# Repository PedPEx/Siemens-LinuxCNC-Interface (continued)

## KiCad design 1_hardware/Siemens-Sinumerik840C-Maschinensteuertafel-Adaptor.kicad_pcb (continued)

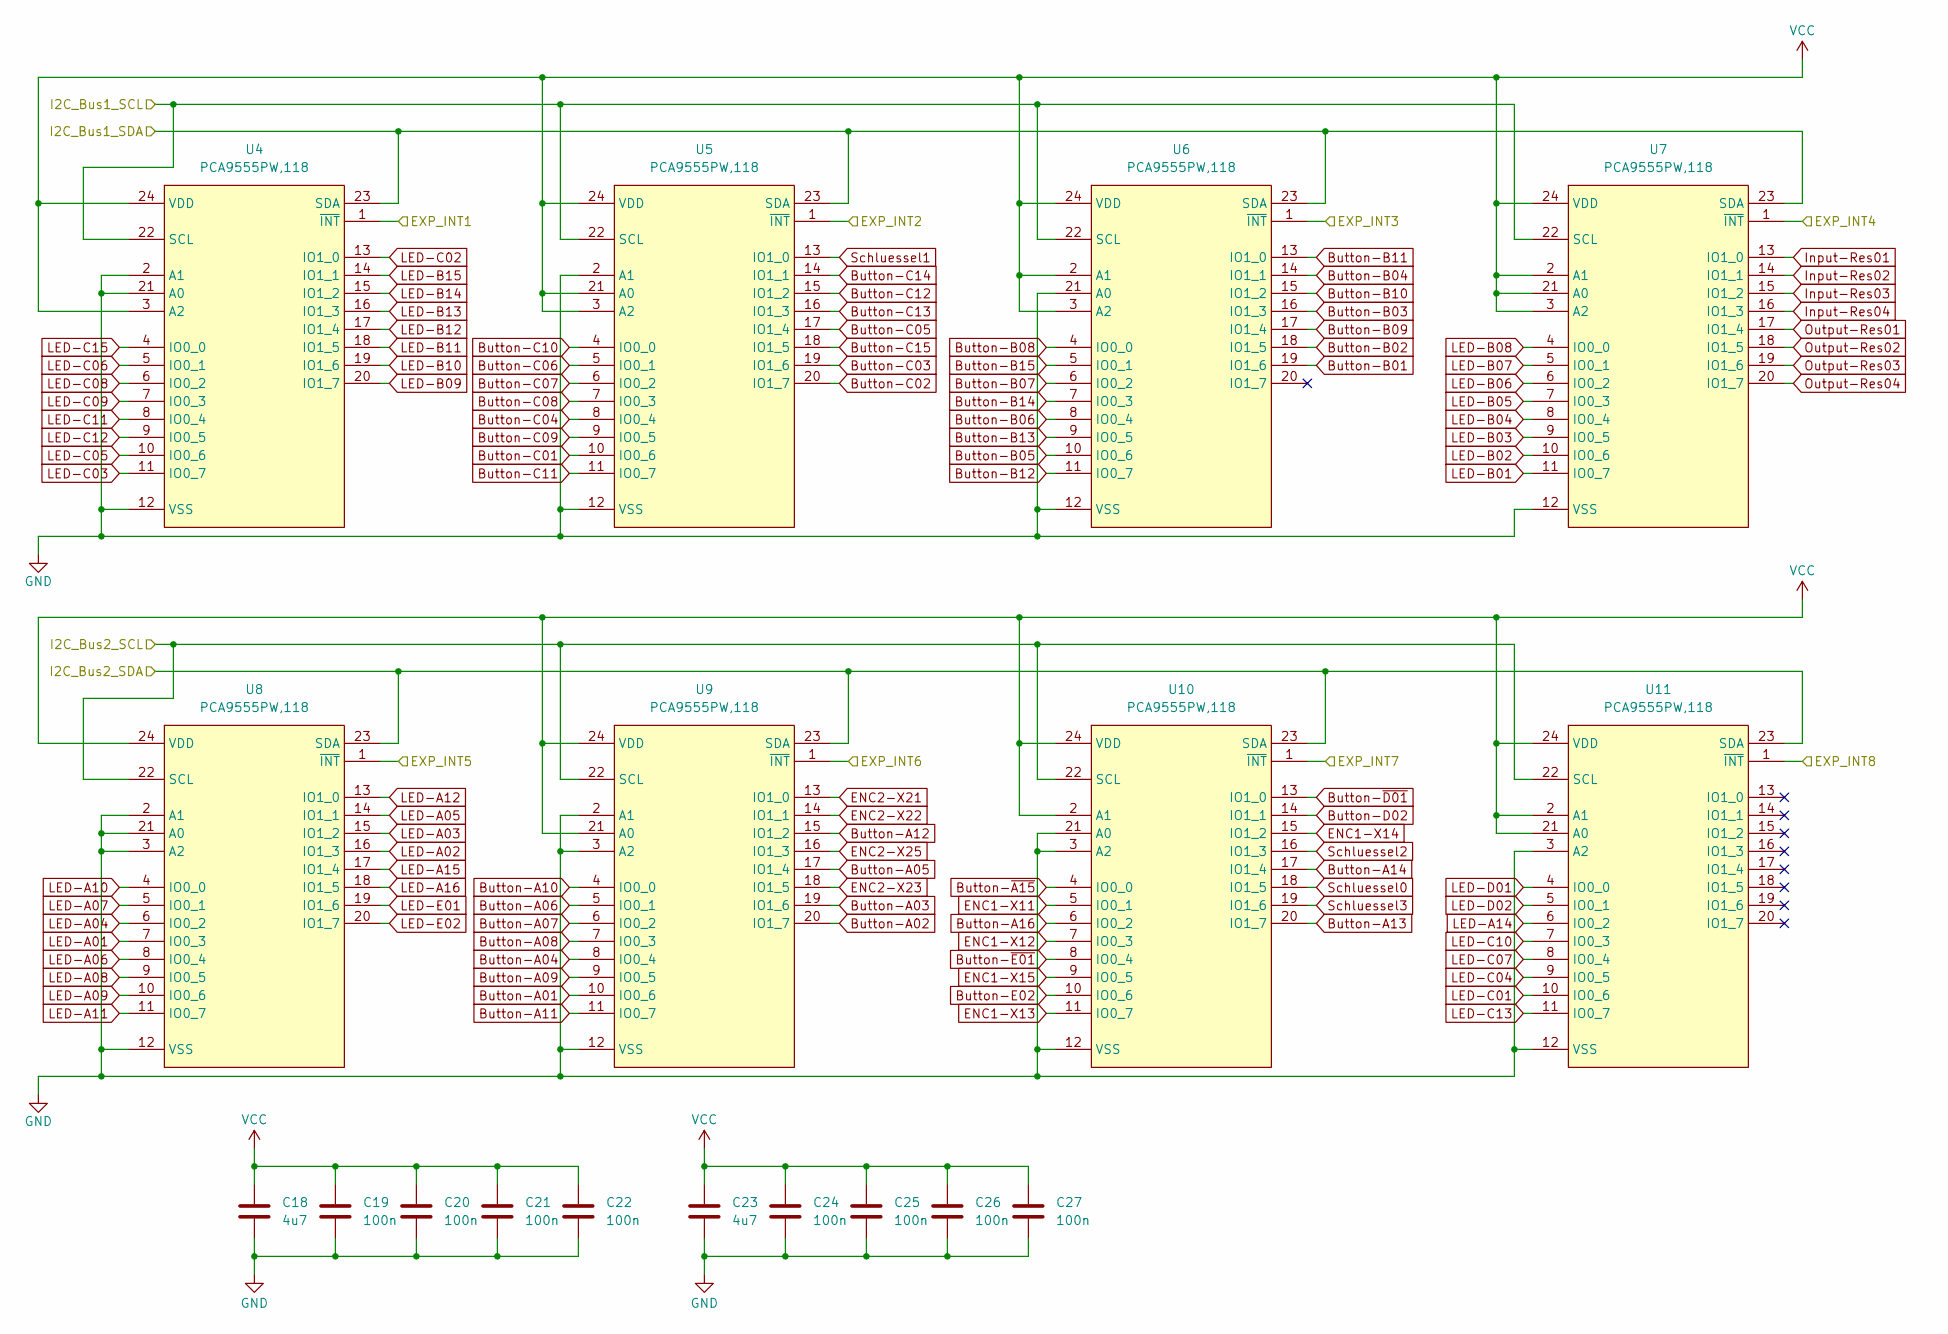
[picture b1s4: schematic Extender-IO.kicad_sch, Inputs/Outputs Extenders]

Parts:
C18, C23: 4u7; C_0603_1608Metric
C19, C20, C21, C22, C24, C25, C26, C27: 100n; C_0603_1608Metric
U4, U5, U6, U7, U8, U9, U10, U11: PCA9555PW,118; TSSOP-24_L7.8-W4.4-P0.65-LS6.4-BL; LCSC Part C128392

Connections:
Button-A01: U9.10 (IO0_6); also elsewhere on the board
Button-A02: U9.20 (IO1_7); also elsewhere on the board
Button-A03: U9.19 (IO1_6); also elsewhere on the board
Button-A04: U9.8 (IO0_4); also elsewhere on the board
Button-A05: U9.17 (IO1_4); also elsewhere on the board
Button-A06: U9.5 (IO0_1); also elsewhere on the board
Button-A07: U9.6 (IO0_2); also elsewhere on the board
Button-A08: U9.7 (IO0_3); also elsewhere on the board
Button-A09: U9.9 (IO0_5); also elsewhere on the board
Button-A10: U9.4 (IO0_0); also elsewhere on the board
Button-A11: U9.11 (IO0_7); also elsewhere on the board
Button-A12: U9.15 (IO1_2); also elsewhere on the board
Button-A13: U10.20 (IO1_7); also elsewhere on the board
Button-A14: U10.17 (IO1_4); also elsewhere on the board
Button-A16: U10.6 (IO0_2); also elsewhere on the board
Button-B01: U6.19 (IO1_6); also elsewhere on the board
Button-B02: U6.18 (IO1_5); also elsewhere on the board
Button-B03: U6.16 (IO1_3); also elsewhere on the board
Button-B04: U6.14 (IO1_1); also elsewhere on the board
Button-B05: U6.10 (IO0_6); also elsewhere on the board
Button-B06: U6.8 (IO0_4); also elsewhere on the board
Button-B07: U6.6 (IO0_2); also elsewhere on the board
Button-B08: U6.4 (IO0_0); also elsewhere on the board
Button-B09: U6.17 (IO1_4); also elsewhere on the board
Button-B10: U6.15 (IO1_2); also elsewhere on the board
Button-B11: U6.13 (IO1_0); also elsewhere on the board
Button-B12: U6.11 (IO0_7); also elsewhere on the board
Button-B13: U6.9 (IO0_5); also elsewhere on the board
Button-B14: U6.7 (IO0_3); also elsewhere on the board
Button-B15: U6.5 (IO0_1); also elsewhere on the board
Button-C01: U5.10 (IO0_6); also elsewhere on the board
Button-C02: U5.20 (IO1_7); also elsewhere on the board
Button-C03: U5.19 (IO1_6); also elsewhere on the board
Button-C04: U5.8 (IO0_4); also elsewhere on the board
Button-C05: U5.17 (IO1_4); also elsewhere on the board
Button-C06: U5.5 (IO0_1); also elsewhere on the board
Button-C07: U5.6 (IO0_2); also elsewhere on the board
Button-C08: U5.7 (IO0_3); also elsewhere on the board
Button-C09: U5.9 (IO0_5); also elsewhere on the board
Button-C10: U5.4 (IO0_0); also elsewhere on the board
Button-C11: U5.11 (IO0_7); also elsewhere on the board
Button-C12: U5.15 (IO1_2); also elsewhere on the board
Button-C13: U5.16 (IO1_3); also elsewhere on the board
Button-C14: U5.14 (IO1_1); also elsewhere on the board
Button-C15: U5.18 (IO1_5); also elsewhere on the board
Button-D02: U10.14 (IO1_1); also elsewhere on the board
Button-E02: U10.10 (IO0_6); also elsewhere on the board
Button-~A15: U10.4 (IO0_0); also elsewhere on the board
Button-~D01: U10.13 (IO1_0); also elsewhere on the board
Button-~E01: U10.8 (IO0_4); also elsewhere on the board
ENC1-X11: U10.5 (IO0_1); also elsewhere on the board
ENC1-X12: U10.7 (IO0_3); also elsewhere on the board
ENC1-X13: U10.11 (IO0_7); also elsewhere on the board
ENC1-X14: U10.15 (IO1_2); also elsewhere on the board
ENC1-X15: U10.9 (IO0_5); also elsewhere on the board
ENC2-X21: U9.13 (IO1_0); also elsewhere on the board
ENC2-X22: U9.14 (IO1_1); also elsewhere on the board
ENC2-X23: U9.18 (IO1_5); also elsewhere on the board
ENC2-X25: U9.16 (IO1_3); also elsewhere on the board
EXP_INT1: U4.1 (~INT); also elsewhere on the board
EXP_INT2: U5.1 (~INT); also elsewhere on the board
EXP_INT3: U6.1 (~INT); also elsewhere on the board
EXP_INT4: U7.1 (~INT); also elsewhere on the board
EXP_INT5: U8.1 (~INT); also elsewhere on the board
EXP_INT6: U9.1 (~INT); also elsewhere on the board
EXP_INT7: U10.1 (~INT); also elsewhere on the board
EXP_INT8: U11.1 (~INT); also elsewhere on the board
GND: C18.1, C19.1, C20.1, C21.1, C22.1, C23.1, C24.1, C25.1, C26.1, C27.1, U4.2 (A1), U4.12 (VSS), U4.21 (A0), U5.2 (A1), U5.12 (VSS), U6.12 (VSS), U6.21 (A0), U7.12 (VSS), U8.2 (A1), U8.3 (A2), U8.12 (VSS), U8.21 (A0), U9.2 (A1), U9.3 (A2), U9.12 (VSS), U10.3 (A2), U10.12 (VSS), U10.21 (A0), U11.3 (A2), U11.12 (VSS); also elsewhere on the board
I2C1_SCL: U4.22 (SCL), U5.22 (SCL), U6.22 (SCL), U7.22 (SCL); also elsewhere on the board
I2C1_SDA: U4.23 (SDA), U5.23 (SDA), U6.23 (SDA), U7.23 (SDA); also elsewhere on the board
I2C2_SCL: U8.22 (SCL), U9.22 (SCL), U10.22 (SCL), U11.22 (SCL); also elsewhere on the board
I2C2_SDA: U8.23 (SDA), U9.23 (SDA), U10.23 (SDA), U11.23 (SDA); also elsewhere on the board
Input-Res01: U7.13 (IO1_0); also elsewhere on the board
Input-Res02: U7.14 (IO1_1); also elsewhere on the board
Input-Res03: U7.15 (IO1_2); also elsewhere on the board
Input-Res04: U7.16 (IO1_3); also elsewhere on the board
LED-A01: U8.7 (IO0_3); also elsewhere on the board
LED-A02: U8.16 (IO1_3); also elsewhere on the board
LED-A03: U8.15 (IO1_2); also elsewhere on the board
LED-A04: U8.6 (IO0_2); also elsewhere on the board
LED-A05: U8.14 (IO1_1); also elsewhere on the board
LED-A06: U8.8 (IO0_4); also elsewhere on the board
LED-A07: U8.5 (IO0_1); also elsewhere on the board
LED-A08: U8.9 (IO0_5); also elsewhere on the board
LED-A09: U8.10 (IO0_6); also elsewhere on the board
LED-A10: U8.4 (IO0_0); also elsewhere on the board
LED-A11: U8.11 (IO0_7); also elsewhere on the board
LED-A12: U8.13 (IO1_0); also elsewhere on the board
LED-A14: U11.6 (IO0_2); also elsewhere on the board
LED-A15: U8.17 (IO1_4); also elsewhere on the board
LED-A16: U8.18 (IO1_5); also elsewhere on the board
LED-B01: U7.11 (IO0_7); also elsewhere on the board
LED-B02: U7.10 (IO0_6); also elsewhere on the board
LED-B03: U7.9 (IO0_5); also elsewhere on the board
LED-B04: U7.8 (IO0_4); also elsewhere on the board
LED-B05: U7.7 (IO0_3); also elsewhere on the board
LED-B06: U7.6 (IO0_2); also elsewhere on the board
LED-B07: U7.5 (IO0_1); also elsewhere on the board
LED-B08: U7.4 (IO0_0); also elsewhere on the board
LED-B09: U4.20 (IO1_7); also elsewhere on the board
LED-B10: U4.19 (IO1_6); also elsewhere on the board
LED-B11: U4.18 (IO1_5); also elsewhere on the board
LED-B12: U4.17 (IO1_4); also elsewhere on the board
LED-B13: U4.16 (IO1_3); also elsewhere on the board
LED-B14: U4.15 (IO1_2); also elsewhere on the board
LED-B15: U4.14 (IO1_1); also elsewhere on the board
LED-C01: U11.10 (IO0_6); also elsewhere on the board
LED-C02: U4.13 (IO1_0); also elsewhere on the board
LED-C03: U4.11 (IO0_7); also elsewhere on the board
LED-C04: U11.9 (IO0_5); also elsewhere on the board
LED-C05: U4.10 (IO0_6); also elsewhere on the board
LED-C06: U4.5 (IO0_1); also elsewhere on the board
LED-C07: U11.8 (IO0_4); also elsewhere on the board
LED-C08: U4.6 (IO0_2); also elsewhere on the board
LED-C09: U4.7 (IO0_3); also elsewhere on the board
LED-C10: U11.7 (IO0_3); also elsewhere on the board
LED-C11: U4.8 (IO0_4); also elsewhere on the board
LED-C12: U4.9 (IO0_5); also elsewhere on the board
LED-C13: U11.11 (IO0_7); also elsewhere on the board
LED-C15: U4.4 (IO0_0); also elsewhere on the board
LED-D01: U11.4 (IO0_0); also elsewhere on the board
LED-D02: U11.5 (IO0_1); also elsewhere on the board
LED-E01: U8.19 (IO1_6); also elsewhere on the board
LED-E02: U8.20 (IO1_7); also elsewhere on the board
Output-Res01: U7.17 (IO1_4); also elsewhere on the board
Output-Res02: U7.18 (IO1_5); also elsewhere on the board
Output-Res03: U7.19 (IO1_6); also elsewhere on the board
Output-Res04: U7.20 (IO1_7); also elsewhere on the board
Schluessel0: U10.18 (IO1_5); also elsewhere on the board
Schluessel1: U5.13 (IO1_0); also elsewhere on the board
Schluessel2: U10.16 (IO1_3); also elsewhere on the board
Schluessel3: U10.19 (IO1_6); also elsewhere on the board
VCC: C18.2, C19.2, C20.2, C21.2, C22.2, C23.2, C24.2, C25.2, C26.2, C27.2, U4.3 (A2), U4.24 (VDD), U5.3 (A2), U5.21 (A0), U5.24 (VDD), U6.2 (A1), U6.3 (A2), U6.24 (VDD), U7.2 (A1), U7.3 (A2), U7.21 (A0), U7.24 (VDD), U8.24 (VDD), U9.21 (A0), U9.24 (VDD), U10.2 (A1), U10.24 (VDD), U11.2 (A1), U11.21 (A0), U11.24 (VDD); also elsewhere on the board

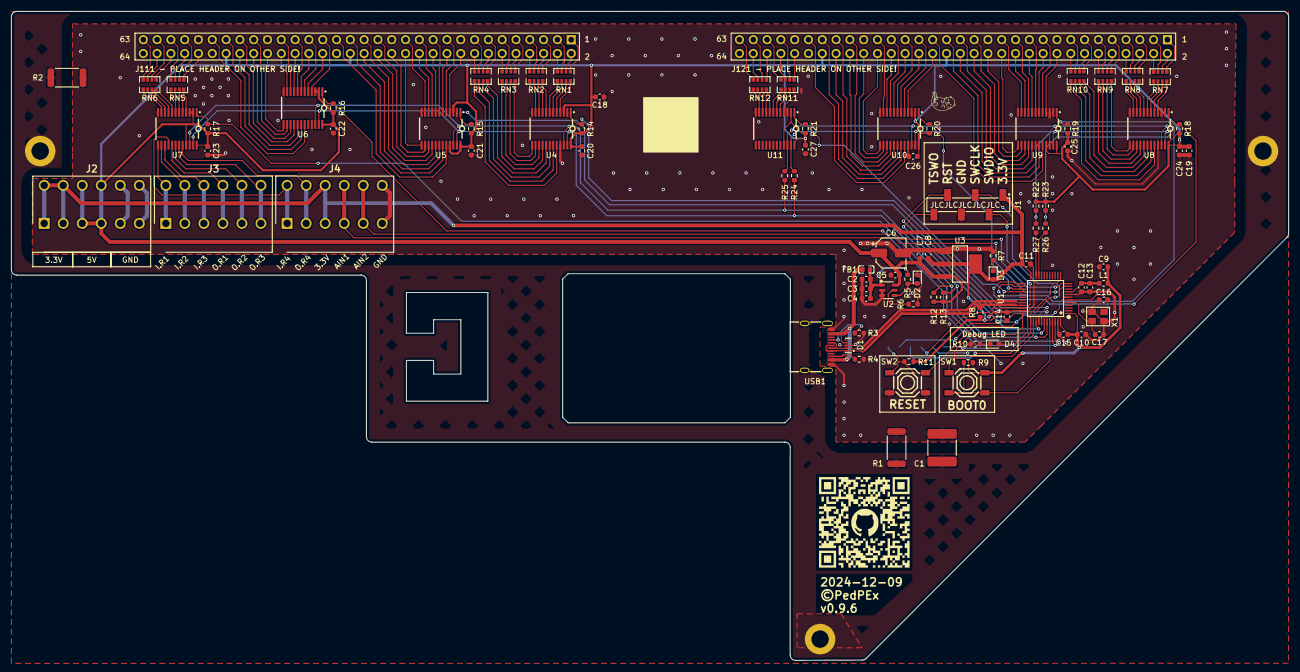
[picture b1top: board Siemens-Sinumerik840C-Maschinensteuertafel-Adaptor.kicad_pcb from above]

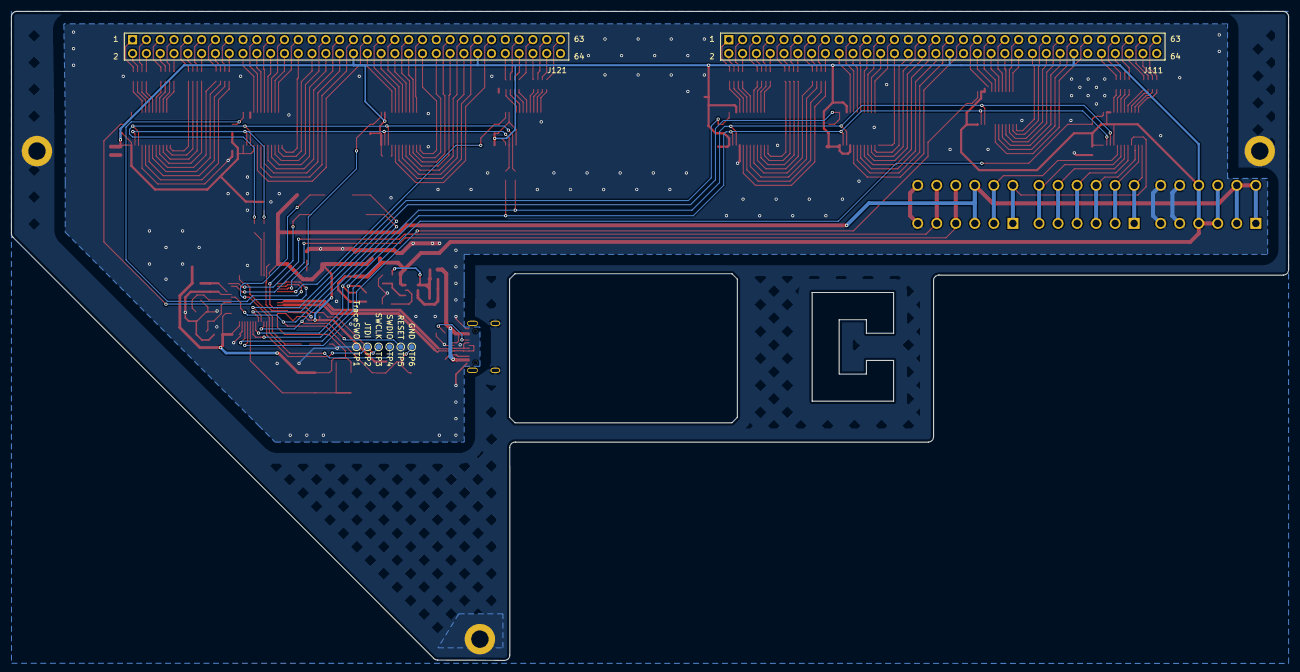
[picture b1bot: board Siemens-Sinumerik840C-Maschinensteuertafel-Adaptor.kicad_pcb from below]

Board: 2 copper layers, 235.0 x 119.4 mm, 102 parts (8 on the bottom side), 207 nets.

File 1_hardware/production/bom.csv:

Designator,Footprint,Quantity,Value,LCSC Part #
C1,2220,1,0.1u,C5290327
"C10, C11, C13, C14, C15, C19, C20, C21, C22, C24, C25, C26, C27",0603,13,100n,
"C12, C2",0603,2,1u,
"C16, C17",0603,2,8p,
"C18, C23, C9",0603,3,4u7,
"C3, C8",0603,2,10u,
"C4, C5, C7",0603,3,0.1u,
C6,CP_Elec_5x5.8,1,100u,C336771
D1,USON-10_L2.5-W1.0-P0.50-BL,1,TPD4E05U06DQAR_C138714,C138714
"D2, D3, D4",0603,3,LED,
FB1,L0603,1,100R@100MHz,C107332
J1,HDR-SMD_6P-P2.54-V-M-LS4.8_R2,1,ProgHeader,C2883763
"J111, J121",SAMTEC_SSW-132-24-L-D,2,SSW-132-24-L-D,
J2,1824460000 - LSF-SMT 3.500690 3.5SN BK TU,1,Power,
J3,1824460000 - LSF-SMT 3.500690 3.5SN BK TU,1,Buttons,
J4,1824460000 - LSF-SMT 3.500690 3.5SN BK TU,1,Reserve2,
L1,0603,1,27nH,C12100
"R1, R2",2512,2,100k, C25717
"R10, R7",0603,2,470,
"R11, R14, R15, R16, R17, R18, R19, R20, R21, R9",0603,10,10k,
"R12, R13, R22, R23, R8",0603,5,1k5,
"R24, R25, R26, R27",0603,4,0,
"R3, R4",0603,2,5k1,
R5,0603,1,680,
R6,0603,1,25k,
"RN1, RN10, RN11, RN12, RN2, RN3, RN4, RN5, RN6, RN7, RN8, RN9",RES-ARRAY-SMD_0603-8P-L3.2-W1.6-BL,12,4x680R,C12035
"SW1, SW2",SW-SMD_4P-L5.1-W5.1-P3.70-LS6.5-TL-2,2,TS-1187A-B-A-B,C318884
TP1,TestPoint_Pad_D1.0mm,1,GND,
TP2,TestPoint_Pad_D1.0mm,1,JTDI,
TP3,TestPoint_Pad_D1.0mm,1,JTMS-SWDIO,
TP4,TestPoint_Pad_D1.0mm,1,JTCK-SWCLK,
TP5,TestPoint_Pad_D1.0mm,1,JTDO-TraceSWO,
TP6,TestPoint_Pad_D1.0mm,1,RESET,
U1,LQFP-48_L7.0-W7.0-P0.50-LS9.0-BL,1,STM32L151C8T6,C9861
"U10, U11, U4, U5, U6, U7, U8, U9",TSSOP-24_L7.8-W4.4-P0.65-LS6.4-BL,8,"PCA9555PW,118",C128392
U2,SOT-23-6_L2.9-W1.6-P0.95-LS2.8-BL,1,AP22652AW6-7,C5329413
U3,SOT-223-4_L6.5-W3.5-P2.30-LS7.0-BR,1,LD1117S33CTR,C35879
USB1,USB-C-SMD_KH-TYPE-C-16P,1,KH-TYPE-C-16P,C709357
X1,CRYSTAL-SMD_4P-L3.2-W2.5-BL_SIT8008BI,1,16MHz,C498200

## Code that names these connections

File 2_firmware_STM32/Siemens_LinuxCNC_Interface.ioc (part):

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Mcu.Name=STM32L151CCTx
Mcu.Package=LQFP48
Mcu.UserName=STM32L151CCTx
PA1.Mode=IN1
PA1.Signal=ADC_IN1
PA11.Mode=Device
PA11.Signal=USB_DM
PA12.Mode=Device
PA12.Signal=USB_DP
PA13.Mode=JTAG_4_pins
PA13.Signal=SYS_JTMS-SWDIO
PA14.Mode=JTAG_4_pins
PA14.Signal=SYS_JTCK-SWCLK
PA15.Mode=JTAG_4_pins
PA15.Signal=SYS_JTDI
PA2.Mode=IN2
PA2.Signal=ADC_IN2
PA3.GPIOParameters=GPIO_Label
PA3.GPIO_Label=DebugLED
PA3.Signal=GPIO_Output
PB10.Mode=I2C
PB10.Signal=I2C2_SCL
PB11.Mode=I2C
PB11.Signal=I2C2_SDA
PB12.GPIOParameters=GPIO_Label,GPIO_ModeDefaultEXTI
PB12.GPIO_Label=Exp_Int5
PB12.GPIO_ModeDefaultEXTI=GPIO_MODE_IT_FALLING
PB12.Signal=GPXTI12
PB13.GPIOParameters=GPIO_Label,GPIO_ModeDefaultEXTI
PB13.GPIO_Label=Exp_Int6
PB13.GPIO_ModeDefaultEXTI=GPIO_MODE_IT_FALLING
PB13.Signal=GPXTI13
PB14.GPIOParameters=GPIO_Label,GPIO_ModeDefaultEXTI
PB14.GPIO_Label=Exp_Int7
PB14.GPIO_ModeDefaultEXTI=GPIO_MODE_IT_FALLING
PB14.Signal=GPXTI14
PB15.GPIOParameters=GPIO_Label,GPIO_ModeDefaultEXTI
PB15.GPIO_Label=Exp_Int8
PB15.GPIO_ModeDefaultEXTI=GPIO_MODE_IT_FALLING
PB15.Signal=GPXTI15
PB3.Mode=JTAG_4_pins
PB3.Signal=SYS_JTDO-TRACESWO
PB4.GPIOParameters=GPIO_Label,GPIO_ModeDefaultEXTI
PB4.GPIO_Label=Exp_Int1
PB4.GPIO_ModeDefaultEXTI=GPIO_MODE_IT_FALLING
PB4.Signal=GPXTI4
PB5.GPIOParameters=GPIO_Label,GPIO_ModeDefaultEXTI
PB5.GPIO_Label=Exp_Int2
PB5.GPIO_ModeDefaultEXTI=GPIO_MODE_IT_FALLING
PB5.Signal=GPXTI5
PB6.Mode=I2C
PB6.Signal=I2C1_SCL
PB7.Mode=I2C
PB7.Signal=I2C1_SDA
PB8.GPIOParameters=GPIO_Label,GPIO_ModeDefaultEXTI
PB8.GPIO_Label=Exp_Int3
PB8.GPIO_ModeDefaultEXTI=GPIO_MODE_IT_FALLING
PB8.Signal=GPXTI8
PB9.GPIOParameters=GPIO_Label,GPIO_ModeDefaultEXTI
PB9.GPIO_Label=Exp_Int4
PB9.GPIO_ModeDefaultEXTI=GPIO_MODE_IT_FALLING
PB9.Signal=GPXTI9
PH0-OSC_IN.Mode=HSE-External-Oscillator
PH0-OSC_IN.Signal=RCC_OSC_IN
PH1-OSC_OUT.Mode=HSE-External-Oscillator
PH1-OSC_OUT.Signal=RCC_OSC_OUT
RCC.HSE_VALUE=16000000
RCC.SYSCLKFreq_VALUE=32000000
RCC.SYSCLKSource=RCC_SYSCLKSOURCE_PLLCLK
board=custom

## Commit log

2024-09-02 init
2024-09-02 fixed typo in link
2024-09-02 fixed faulty link
2024-09-02 finished most of schematic, init STM32 program
2024-09-05 finished schematics and board
2024-09-05 new render
2024-09-07 changed from STM32F103C8 over to STM32L151C8 changed controller pinout, minor tweaks in board design, added labels and debug pads
2024-09-07 added pictures and updated rendering
2024-10-18 finished v0.9.2
2024-10-18 pcb v0.9.3 finished
2024-10-25 PCB v0.9.4 - finished final prototype STM32 project reinitialised (F103C8 -> L151C8)
2024-10-27 PCB v0.9.5 - finished final prototype STM32 project pinout corrected
2025-03-06 started with PCB v0.9.6, software WIP communication with expander working, able to read inputs and set outputs, matrix for properly key-mapping and serial still needs to be done bugs from first badge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
2025-03-06 updated gitignore
2025-03-07 setting outputs via serial working, inputs ToDo the outputs can now be set via the serial console, all LUTs are finished, input serial messaging ToDo serial protocol from LinuxCNC_ArduinoConnector im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
2025-03-07 serial protocol working, commands working ToDo: Analog Inputs and ENC not yet implemented or not readable in own variable
2025-03-09 minor tweaks and improvements
2025-03-15 encoder working, problems with sending init state The encoders return their values, position as well as printed value on interface. Found a limitation in the STM32 USB_CDC HAL library, the controler 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
2025-03-21 software functionally completed, more details... software needs cleanup an timeout detection on LinuxCNC side
2025-03-22 added animations for waiting and lost connection
